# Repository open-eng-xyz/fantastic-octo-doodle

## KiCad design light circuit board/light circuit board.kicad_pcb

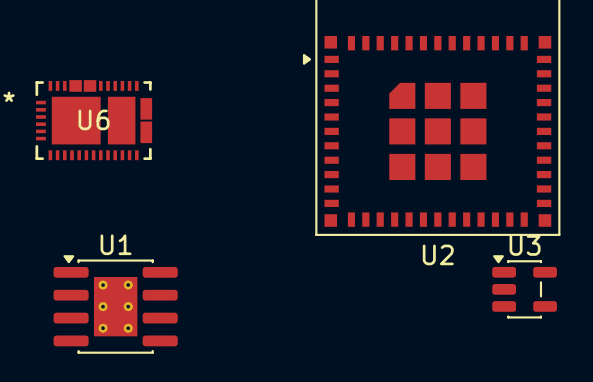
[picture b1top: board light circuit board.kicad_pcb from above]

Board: 2 copper layers, 4 parts (0 on the bottom side), 14 nets, no tracks yet.

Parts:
U1: TP4056-42-ESOP8; SOIC-8-1EP_3.9x4.9mm_P1.27mm_EP2.41x3.3mm_ThermalVias
U2: ESP32-C6-MINI-1
U3: AP2112K-3.3; SOT-23-5
U6: TPS25730ADREFR; WQFN-38_REF0038A_TEX

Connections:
+5V: U6.20 (PPHV), U6.21 (PPHV), U6.22 (PPHV)
/3v3regulated: U2.3 (3V3), U2.8 (EN), U3.5 (VOUT), U6.38 (VIN_3V3)
/cap_mis: U2.19 (IO14), U6.6 (CAP_MIS)
/dbg_acc: U2.20 (IO15), U6.10 (DBG_ACC)
/drain: U6.15 (DRAIN), U6.40 (EPAD)
/ldo_3v3: U6.1 (LDO_3V3), U6.27 (PD5VMAX)
/plug_event: U2.17 (IO12), U6.37 (PLUG_EVENT)
/plug_flip: U2.18 (IO13), U6.13 (PLUG_FLIP)
/sink_en: U2.16 (IO7), U6.19 (*SINK_EN)
/vbus: U6.23 (VBUS_IN), U6.24 (VBUS_IN), U6.25 (VBUS_IN), U6.32 (VBUS), U6.33 (VBUS)
GND: U1.3 (GND), U3.2 (GND), U6.11 (GND), U6.12 (GND), U6.14 (GND), U6.16 (GND), U6.17 (GND), U6.31 (GND), U6.34 (GND), U6.35 (GND), U6.39 (GND)
unnamed: U1.4 (V_{CC}), U1.8 (CE)
unnamed: U2.1 (GND), U2.2 (GND), U2.11 (GND), U2.14 (GND), U2.36 (GND), U2.37 (GND), U2.38 (GND), U2.39 (GND), U2.40 (GND), U2.41 (GND), U2.42 (GND), U2.43 (GND), U2.44 (GND), U2.45 (GND), U2.46 (GND), U2.47 (GND), U2.48 (GND), U2.49 (GND), U2.50 (GND), U2.51 (GND), U2.52 (GND), U2.53 (GND)
VCC: U1.5 (BAT), U3.1 (VIN), U3.3 (EN)
